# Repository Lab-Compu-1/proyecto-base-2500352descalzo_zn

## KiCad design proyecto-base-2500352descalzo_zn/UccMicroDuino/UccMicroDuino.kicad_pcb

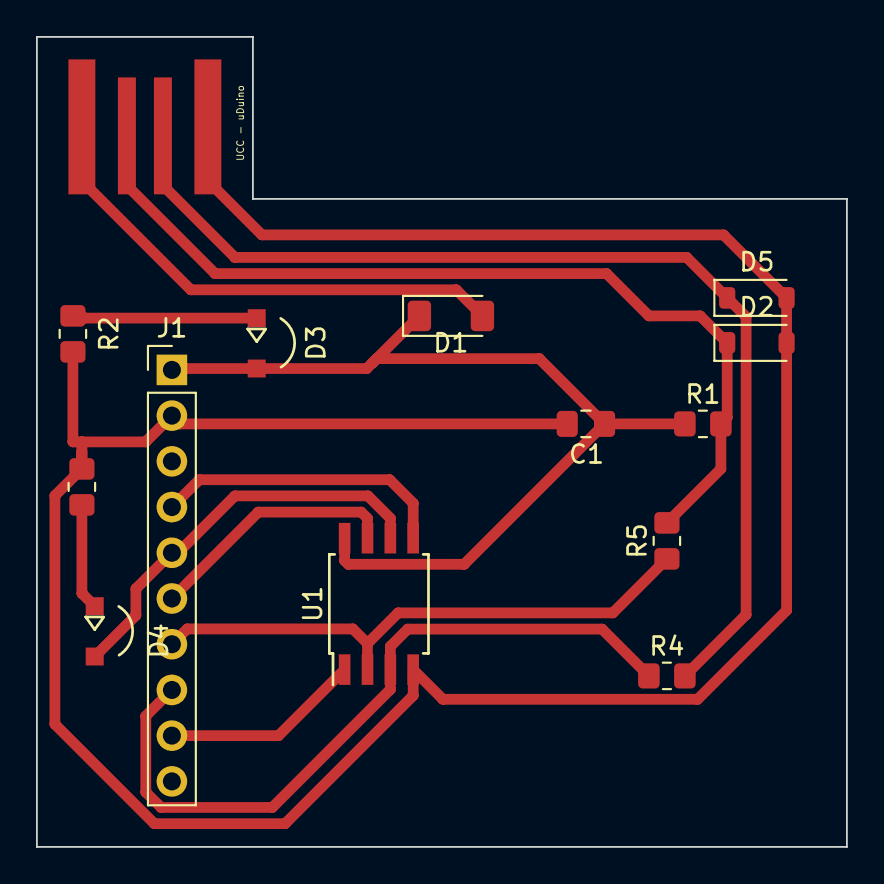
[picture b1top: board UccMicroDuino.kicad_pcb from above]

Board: 2 copper layers, 45.0 x 45.0 mm, 14 parts (0 on the bottom side), 13 nets.

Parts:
C1: C 0.1u; C_0805_2012Metric_Pad1.18x1.45mm_HandSolder
D1: D_Filled PMLL4148L; D_MiniMELF
D2, D5: D_Zener 3.6V 1/2mW; D_SOD-123
D3: LED_RED; ledSMD
D4: LED_GREEN; ledSMD
J1: Conn_01x10_Socket HEADER; PinHeader_1x10_P2.54mm_Vertical
J2: USB_PCB_A; USB_A_UCC
R1: R 1.5KQ 5% 1/8W; R_0805_2012Metric_Pad1.20x1.40mm_HandSolder
R2, R3: R 330Q 5% 1/8W; R_0805_2012Metric_Pad1.20x1.40mm_HandSolder
R4, R5: R 68Q 5% 1/8W; R_0805_2012Metric_Pad1.20x1.40mm_HandSolder
U1: ATtiny85-20S; SOIC-8W_5.3x5.3mm_P1.27mm

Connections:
+5V: C1.1, D1.1 (K), D3.2 (A), J1.1, R1.1, U1.8 (VCC)
GND: C1.2, D2.2 (A), D5.2 (A), J1.2, J2.4 (GND), R2.2, R3.2, U1.4 (GND)
unnamed: D1.2 (A), J2.1 (VBUS)
unnamed: D2.1 (K), J2.2 (D-), R1.2, R5.2
unnamed: D3.1 (K), R2.1
unnamed: D4.2 (A), J1.5, U1.6 (PB1)
unnamed: D4.1 (K), R3.1
unnamed: D5.1 (K), J2.3 (D+), R4.2
unnamed: J1.4, U1.5 (AREF/PB0)
unnamed: J1.6, U1.7 (PB2)
unnamed: J1.7, R5.1, U1.2 (XTAL1/PB3)
unnamed: J1.8, R4.1, U1.3 (XTAL2/PB4)
unnamed: J1.9, U1.1 (~RESET/PB5)

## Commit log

2025-03-17 GitHub Classroom Feedback
2025-03-17 Setting up GitHub Classroom Feedback
2025-04-07 plano eléctrico terminado
2025-04-14 Add files via upload
    PLANO ELECTRICO FINAL
2025-04-28 PLACA EDITADA EN LA ESQUINA
2025-05-12 RUTEO CASI TERMINADO, 1 FALTANTE
2025-05-12 RUTEO CASI TERMINADO 1 FALTANTE
2025-05-26 Add files via upload
    PROYECTO KICAD FINAL TERMINADO.
